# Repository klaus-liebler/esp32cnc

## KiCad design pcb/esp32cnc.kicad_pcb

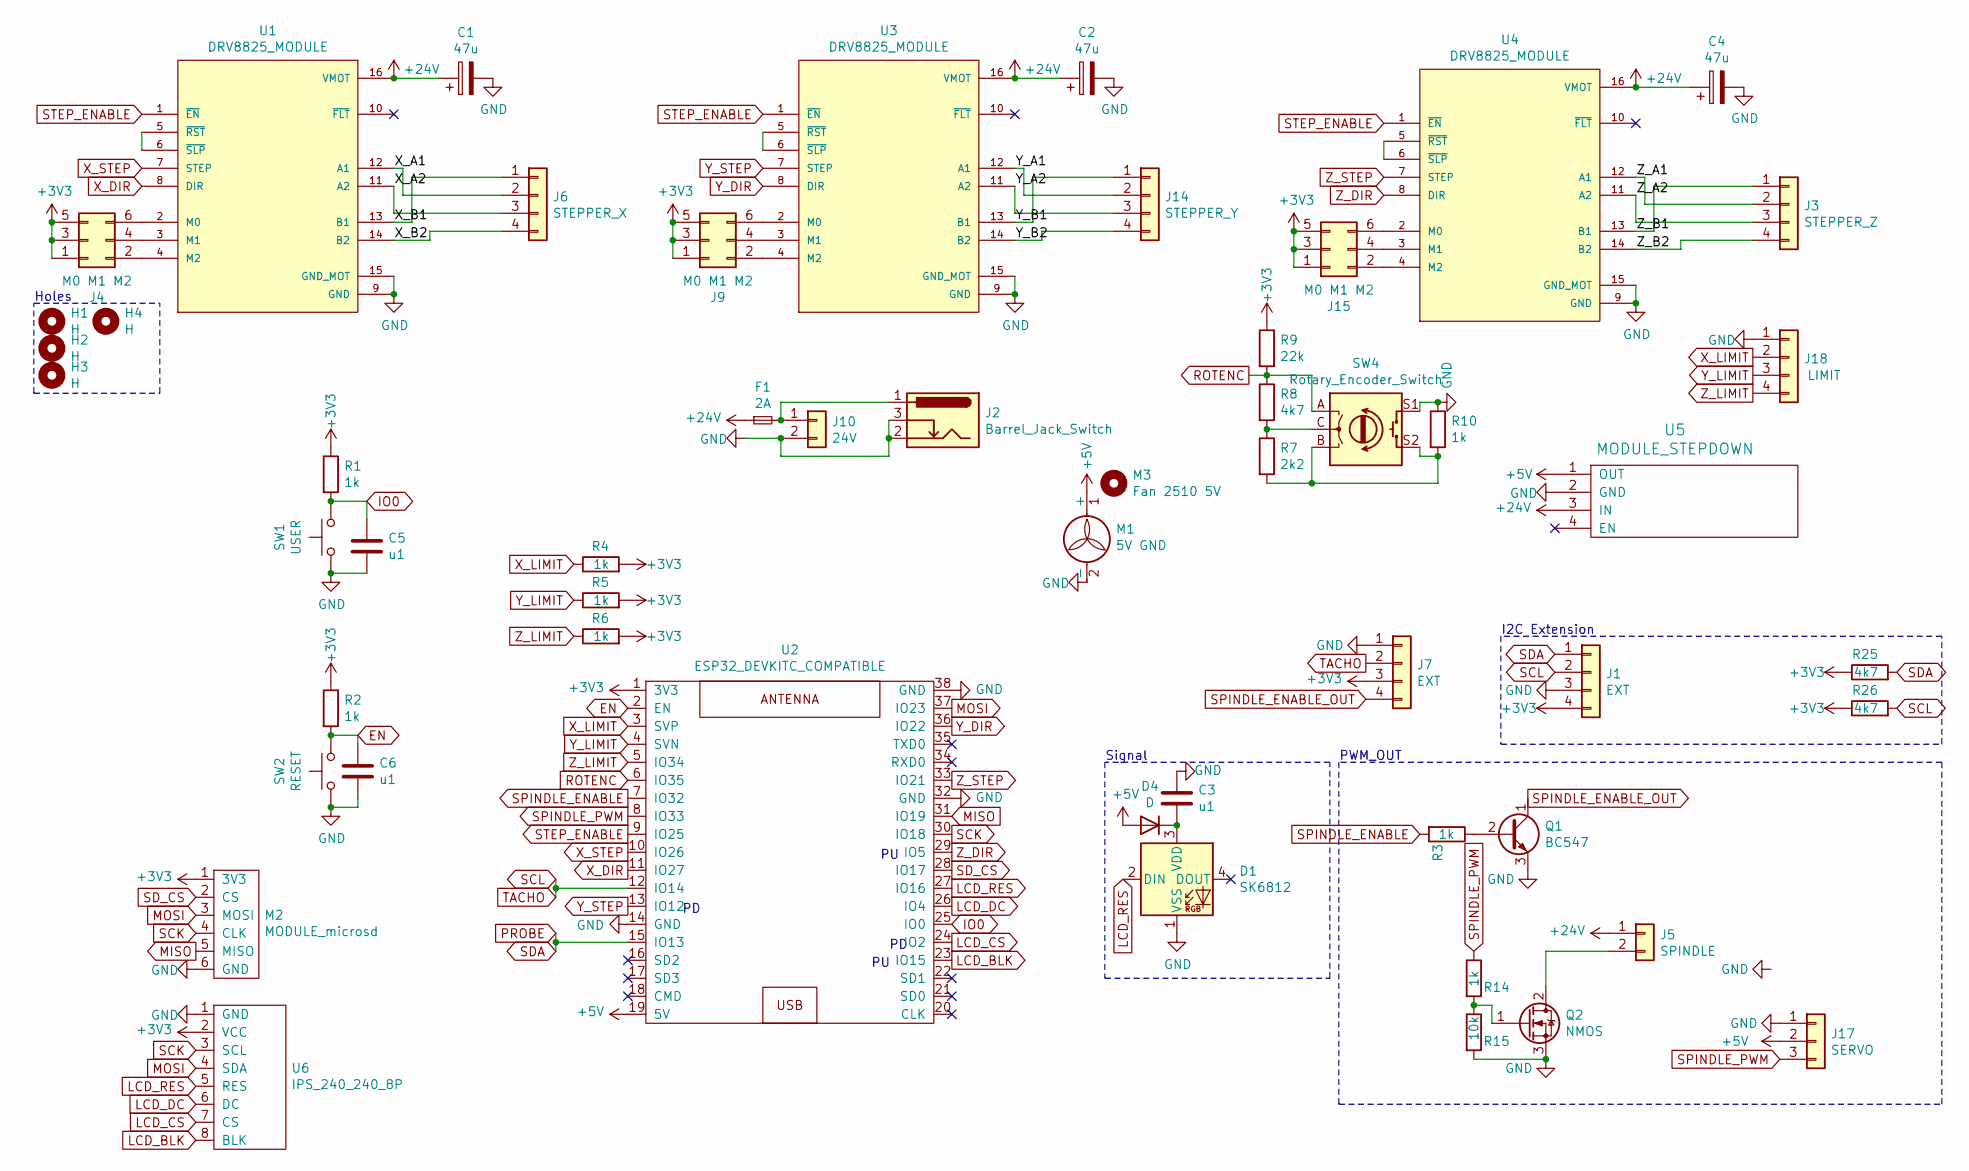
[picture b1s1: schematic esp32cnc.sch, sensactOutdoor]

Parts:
C1, C2, C4: 47u; CP_Radial_D6.3mm_P2.50mm
C3, C5, C6: u1; C_Rect_L7.0mm_W2.5mm_P5.00mm
D1: SK6812; LED_D5.0mm-4_RGB_Staggered_Pins
D4: D; D_DO-35_SOD27_P7.62mm_Horizontal
F1: 2A; Fuseholder5x20_horiz_open_inline_Type-I
H1, H2, H3, H4: H; MountingHole_3.2mm_M3
J1, J7: EXT; JST_XH_B4B-XH-A_1x04_P2.50mm_Vertical
J2: Barrel_Jack_Switch; BarrelJack_Horizontal
J3: STEPPER_Z; JST_XH_B4B-XH-A_1x04_P2.50mm_Vertical
J4, J9, J15: M0 M1 M2; PinHeader_2x03_P2.54mm_Vertical
J5: SPINDLE; PhoenixContact_MC_1,5_2-G-3.5_1x02_P3.50mm_Horizontal
J6: STEPPER_X; JST_XH_B4B-XH-A_1x04_P2.50mm_Vertical
J10: 24V; PhoenixContact_MSTBV_2,5_2-G-5,08_1x02_P5.08mm_Vertical
J14: STEPPER_Y; JST_XH_B4B-XH-A_1x04_P2.50mm_Vertical
J17: SERVO; PinHeader_1x03_P2.54mm_Vertical
J18: LIMIT; JST_XH_B4B-XH-A_1x04_P2.50mm_Vertical
M1: 5V GND; JST_XH_B2B-XH-AM_1x02_P2.50mm_Vertical
M2: MODULE_microsd
M3: Fan 2510 5V; FAN_2510
Q1: BC547; TO-92_HandSolder
Q2: NMOS; TO-220F-3_Vertical
R1, R2, R3, R4, R5, R6, R10, R14: 1k; R_Axial_DIN0207_L6.3mm_D2.5mm_P7.62mm_Horizontal
R7: 2k2; R_Axial_DIN0207_L6.3mm_D2.5mm_P7.62mm_Horizontal
R8, R25, R26: 4k7; R_Axial_DIN0207_L6.3mm_D2.5mm_P7.62mm_Horizontal
R9: 22k; R_Axial_DIN0207_L6.3mm_D2.5mm_P7.62mm_Horizontal
R15: 10k; R_Axial_DIN0207_L6.3mm_D2.5mm_P7.62mm_Horizontal
SW1: USER; SW_PUSH_6mm_H13mm
SW2: RESET; SW_PUSH_6mm_H13mm
SW4: Rotary_Encoder_Switch; RotaryEncoder_Alps_EC11E-Switch_Vertical_H20mm
U1, U3, U4: DRV8825_MODULE; IC_DRV8825_STEPPER_MOTOR_DRIVER_CARRIER
U2: ESP32_DEVKITC_COMPATIBLE
U5: MODULE_STEPDOWN
U6: IPS_240_240_8P; IPS_240_240_2.0

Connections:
+3V3: J1.4, J4.1, J4.3, J4.5, J7.3, J9.1, J9.3, J9.5, J15.1, J15.3, J15.5, M2.1 (3V3), R1.1, R2.1, R4.2, R5.2, R6.2, R9.1, R25.1, R26.1, U2.1 (3V3), U6.2 (VCC)
+5V: D4.2 (A), J17.2, M1.1 (+), U2.19 (5V), U5.1 (OUT)
+24V: C1.1, C2.1, C4.1, F1.1, J5.1, U1.16 (VMOT), U3.16 (VMOT), U4.16 (VMOT), U5.3 (IN)
/X_A1: J6.2, U1.12 (A1)
/X_A2: J6.3, U1.11 (A2)
/X_B1: J6.1, U1.13 (B1)
/X_B2: J6.4, U1.14 (B2)
/Y_A1: J14.2, U3.12 (A1)
/Y_A2: J14.3, U3.11 (A2)
/Y_B1: J14.1, U3.13 (B1)
/Y_B2: J14.4, U3.14 (B2)
/Z_A1: J3.2, U4.12 (A1)
/Z_A2: J3.3, U4.11 (A2)
/Z_B1: J3.1, U4.13 (B1)
/Z_B2: J3.4, U4.14 (B2)
EN: C6.1, R2.2, SW2.2, U2.2 (EN)
GND: C1.2, C2.2, C3.1, C4.2, C5.2, C6.2, D1.1 (VSS), J1.3, J2.2, J2.3, J7.1, J10.2, J17.1, J18.1, M1.2 (-), M2.6 (GND), Q1.3 (E), Q2.3 (S), R10.1, R15.2, SW1.1, SW2.1, SW4.S1, U1.9 (GND), U1.15 (GND_MOT), U2.14 (GND), U2.32 (GND), U2.38 (GND), U3.9 (GND), U3.15 (GND_MOT), U4.9 (GND), U4.15 (GND_MOT), U5.2 (GND), U6.1 (GND)
IO0: C5.1, R1.2, SW1.2, U2.25 (IO0)
LCD_BLK: U2.23 (IO15), U6.8 (BLK)
LCD_CS: U2.24 (IO2), U6.7 (CS)
LCD_DC: U2.26 (IO4), U6.6 (DC)
LCD_RES: D1.2 (DIN), U2.27 (IO16), U6.5 (RES)
MISO: M2.5 (MISO), U2.31 (IO19)
MOSI: M2.3 (MOSI), U2.37 (IO23), U6.4 (SDA)
unnamed: C3.2, D1.3 (VDD), D4.1 (K)
unnamed: F1.2, J2.1, J10.1
unnamed: J4.2, U1.4 (M2)
unnamed: J4.4, U1.3 (M1)
unnamed: J4.6, U1.2 (M0)
unnamed: J5.2, Q2.2 (D)
unnamed: J9.2, U3.4 (M2)
unnamed: J9.4, U3.3 (M1)
unnamed: J9.6, U3.2 (M0)
unnamed: J15.2, U4.4 (M2)
unnamed: J15.4, U4.3 (M1)
unnamed: J15.6, U4.2 (M0)
unnamed: Q1.2 (B), R3.1
unnamed: Q2.1 (G), R14.2, R15.1
unnamed: R7.1, R8.2, SW4.C
unnamed: R7.2, R10.2, SW4.B, SW4.S2
unnamed: U1.5 (~RST), U1.6 (~SLP)
unnamed: U3.5 (~RST), U3.6 (~SLP)
unnamed: U4.5 (~RST), U4.6 (~SLP)
PROBE: J1.1, R25.2, U2.15 (IO13)
ROTENC: R8.1, R9.2, SW4.A, U2.6 (IO35)
SCK: M2.4 (CLK), U2.30 (IO18), U6.3 (SCL)
SCL: J1.2, J7.2, R26.2, U2.12 (IO14)
SD_CS: M2.2 (CS), U2.28 (IO17)
SPINDLE_ENABLE: R3.2, U2.7 (IO32)
SPINDLE_ENABLE_OUT: J7.4, Q1.1 (C)
SPINDLE_PWM: J17.3, R14.1, U2.8 (IO33)
STEP_ENABLE: U1.1 (~EN), U2.9 (IO25), U3.1 (~EN), U4.1 (~EN)
X_DIR: U1.8 (DIR), U2.11 (IO27)
X_LIMIT: J18.2, R4.1, U2.3 (SVP)
X_STEP: U1.7 (STEP), U2.10 (IO26)
Y_DIR: U2.36 (IO22), U3.8 (DIR)
Y_LIMIT: J18.3, R5.1, U2.4 (SVN)
Y_STEP: U2.13 (IO12), U3.7 (STEP)
Z_DIR: U2.29 (IO5), U4.8 (DIR)
Z_LIMIT: J18.4, R6.1, U2.5 (IO34)
Z_STEP: U2.33 (IO21), U4.7 (STEP)

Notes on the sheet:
PWM_OUT
I2C Extension
Signal
Holes

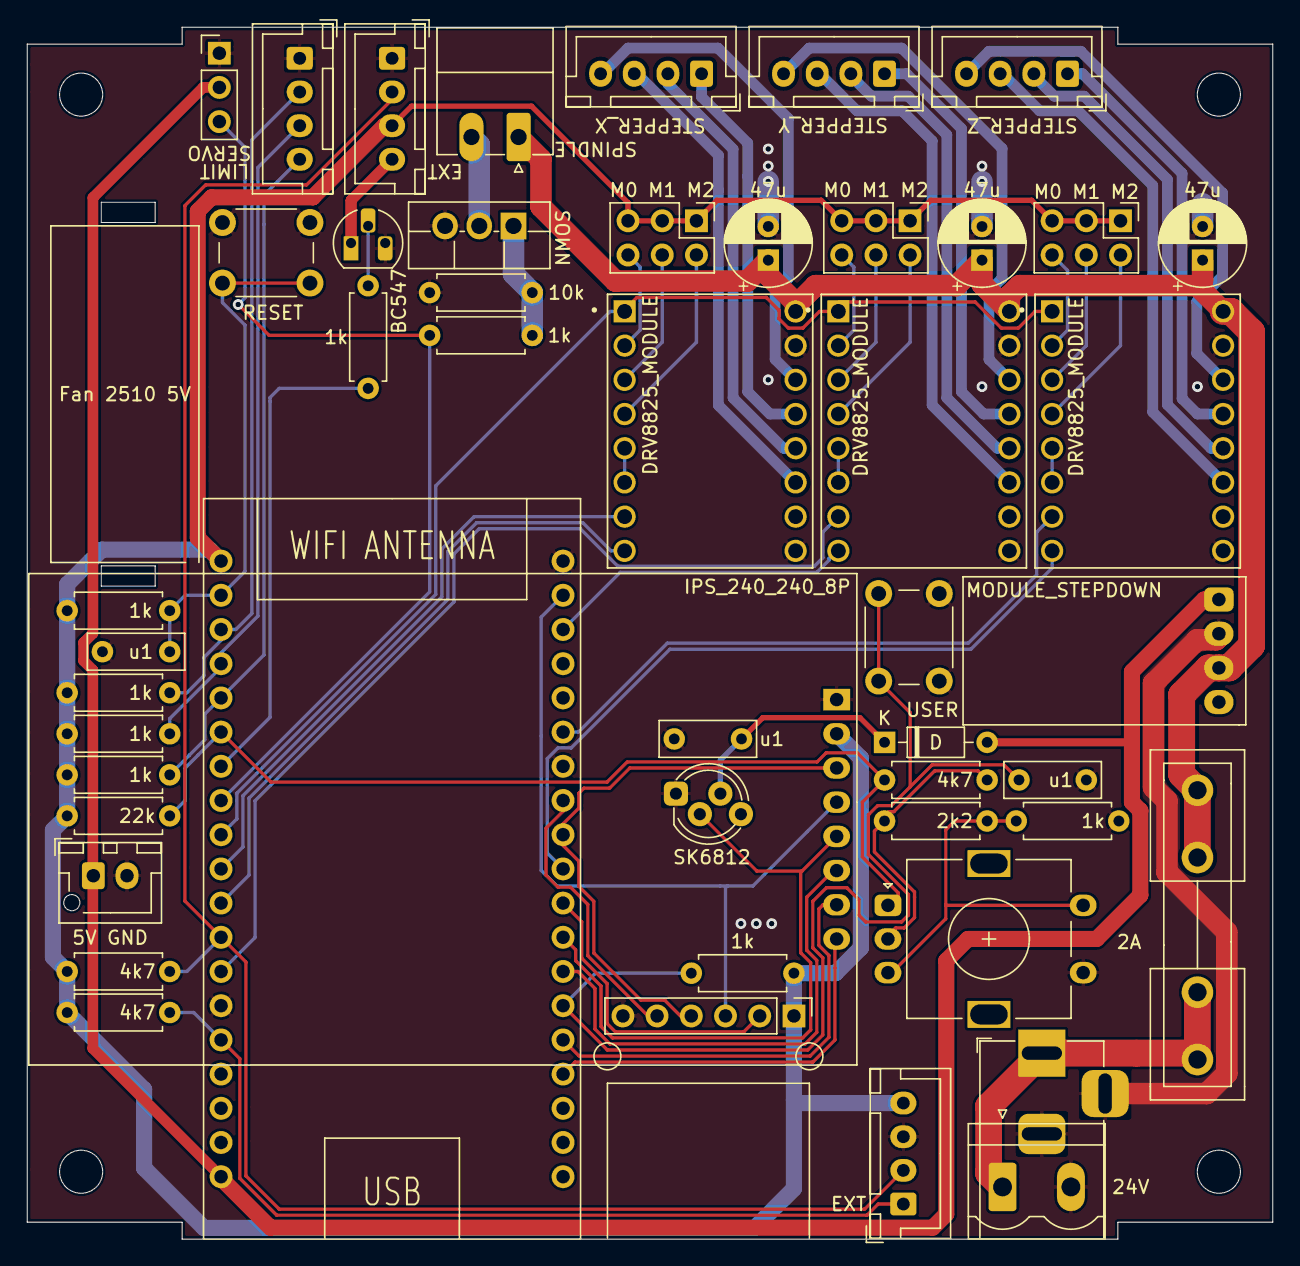
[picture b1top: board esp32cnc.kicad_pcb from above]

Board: 2 copper layers, 92.5 x 90.0 mm, 54 parts (0 on the bottom side), 61 nets.
